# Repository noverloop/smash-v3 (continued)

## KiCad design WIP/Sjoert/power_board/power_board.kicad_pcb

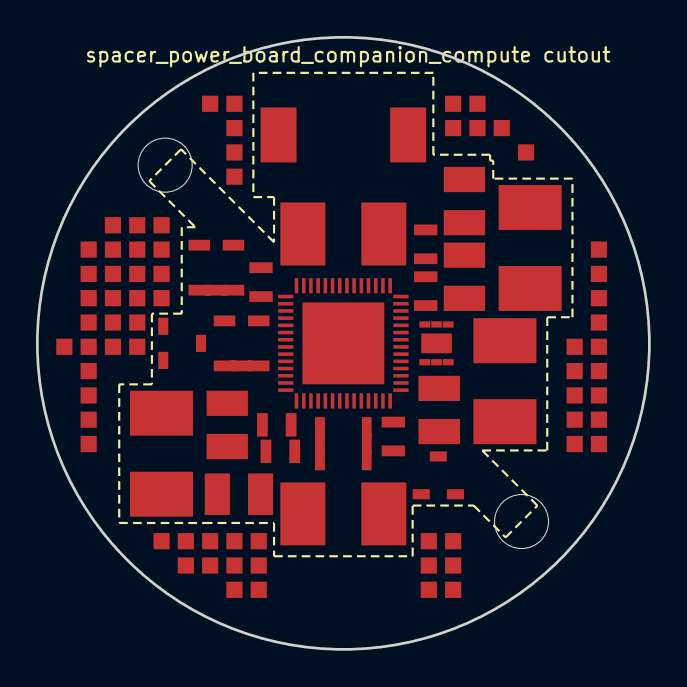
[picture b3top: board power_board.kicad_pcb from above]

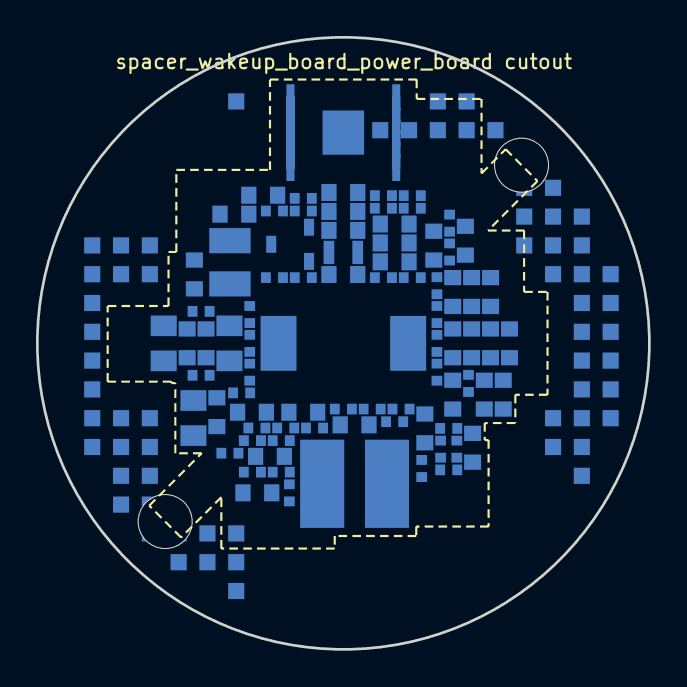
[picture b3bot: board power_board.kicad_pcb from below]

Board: 4 copper layers, 34.0 x 34.0 mm, 109 parts (84 on the bottom side), 95 nets, no tracks yet.

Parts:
CBAT1, CBAT2: T528W 100uF (7343-15 thinnest variant); Capacitor_Tantalum_SMD_CP_EIA-7343-15_Kemet-W
CBAT3: C-Series MIL-PRF-32535 X7R 0805 1uF; Capacitor_SMD_C_0805_2012Metric
C_BAT_BULK1, C_BAT_BULK2: T528W 470uF (7343-15 thinnest variant); Capacitor_Tantalum_SMD_CP_EIA-7343-15_Kemet-W
C_BOOST_COMP: C-Series MIL-PRF-32535 X7R 0603 220nF; Capacitor_SMD_C_0603_1608Metric
C_BOOST_OUT1: T528W 47uF (7343-15 thinnest variant); Capacitor_Tantalum_SMD_CP_EIA-7343-15_Kemet-W
C_BOOST_OUT2_1, C_BOOST_OUT2_2, C_BOOST_OUT2_3, C_BOOST_OUT2_4, C_BOOST_OUT2_5: C-Series MIL-PRF-32535 X7R 0603 2.2uF; Capacitor_SMD_C_0603_1608Metric
C_BOOST_OUT3: C0402 X7R 100nF; Capacitor_SMD_C_0402_1005Metric
C_BOOST_SS: C0402 X7R 47nF; Capacitor_SMD_C_0402_1005Metric
C_CAM_LDO_VAA_IN: C-Series MIL-PRF-32535 X7R 0805 1uF; Capacitor_SMD_C_0805_2012Metric
C_CAM_LDO_VAA_OUT_1, C_CAM_LDO_VAA_OUT_2: C-Series MIL-PRF-32535 X7R 0603 2.2uF; Capacitor_SMD_C_0603_1608Metric
C_CAM_LDO_VDD_IN: C-Series MIL-PRF-32535 X7R 0805 1uF; Capacitor_SMD_C_0805_2012Metric
C_CAM_LDO_VDD_OUT: C-Series MIL-PRF-32535 X7R 0603 2.2uF; Capacitor_SMD_C_0603_1608Metric
C_PMIC_0V9_1, C_PMIC_0V82_1, C_PMIC_1V8_1, C_PMIC_3V3_1: T491T 22uF (3528-12 thinnest variant); Capacitor_Tantalum_SMD_CP_EIA-3528-12_Kemet-T
C_PMIC_0V9_2, C_PMIC_0V82_2, C_PMIC_1V2_2, C_PMIC_1V8_2, C_PMIC_2V8_2, C_PMIC_3V3_2: C0402 X7R 100nF; Capacitor_SMD_C_0402_1005Metric
C_PMIC_1V2_1_1, C_PMIC_1V2_1_2, C_PMIC_1V2_1_3, C_PMIC_1V2_1_4, C_PMIC_1V2_1_5, C_PMIC_2V8_1_1, C_PMIC_2V8_1_2, C_PMIC_5V_FILT_1, C_PMIC_5V_FILT_2, C_PMIC_5V_FILT_3, C_PMIC_5V_FILT_4, C_PMIC_5V_FILT_5: C-Series MIL-PRF-32535 X7R 0603 2.2uF; Capacitor_SMD_C_0603_1608Metric
C_PMIC_INTLDO_1, C_PMIC_INTLDO_2: C-Series MIL-PRF-32535 X7R 0603 2.2uF; Capacitor_SMD_C_0603_1608Metric
C_PMIC_LDO1, C_PMIC_LDO2, C_PMIC_LDO4, C_PMIC_LDO6, C_PMIC_LDO7, C_PMIC_LDO8: C0402 X7R 100nF; Capacitor_SMD_C_0402_1005Metric
C_PMIC_VIN1: T491T 22uF (3528-12 thinnest variant); Capacitor_Tantalum_SMD_CP_EIA-3528-12_Kemet-T
C_PMIC_VIN2: C0402 X7R 100nF; Capacitor_SMD_C_0402_1005Metric
C_PMIC_VIN3, C_PMIC_VIN4, C_PMIC_VIN5, C_PMIC_VIN6: C-Series MIL-PRF-32535 X7R 0603 2.2uF; Capacitor_SMD_C_0603_1608Metric
C_PMIC_VLX7: C0402 X7R 100nF; Capacitor_SMD_C_0402_1005Metric
C_PMIC_VOUT7: C0402 X7R 100nF; Capacitor_SMD_C_0402_1005Metric
C_PMIC_VPP_1: T491T 22uF (3528-12 thinnest variant); Capacitor_Tantalum_SMD_CP_EIA-3528-12_Kemet-T
C_PMIC_VPP_2: C0402 X7R 100nF; Capacitor_SMD_C_0402_1005Metric
C_TMP1: C0402 X7R 100nF; Capacitor_SMD_C_0402_1005Metric
C_USB_VBUS_1, C_USB_VBUS_2, C_USB_VBUS_3, C_USB_VBUS_4, C_USB_VBUS_5: C-Series MIL-PRF-32535 X7R 0603 2.2uF; Capacitor_SMD_C_0603_1608Metric
D_BOOST_COMP: MBRS540T3G; DIOM7958X256N
D_USB_PWR: MBRS540T3G; DIOM7958X256N
J_power_board_spacer_power_board_companion_compute: LGA_lands; J_power_board_spacer_power_board_companion_compute
L_BOOST_COMP: 744043100; INDPM4848X280N
L_PMIC_BUCK1, L_PMIC_BUCK5, L_PMIC_BUCK6: TMS201210ALM-1R0MTAA; Inductor_SMD_L_2012_2.0x1.25mm
L_PMIC_BUCK2, L_PMIC_BUCK3, L_PMIC_BUCK4: TMS201210ALM-2R2MTAA; Inductor_SMD_L_2012_2.0x1.25mm
L_PMIC_FILT: TMS201210ALM-1R0MTAA; Inductor_SMD_L_2012_2.0x1.25mm
P_power_board_spacer_wakeup_board_power_board: LGA_lands; P_power_board_spacer_wakeup_board_power_board
Q_ISO: DMP6110SVT-7; SOT95P280X100-6N
Q_ISO_DRV: BSS138LT1G; SOT96P237X111-3N
Q_ISO_USB: BSS138LT1G; SOT96P237X111-3N
Q_USB_WAKE: BSS138LT1G; SOT96P237X111-3N
R_BAT1_ISO, R_BAT2_ISO, R_BAT3_ISO: CRCW0402 200m 1% e3; Resistor_SMD_R_0402_1005Metric
R_BOOST_COMP: CRCW0402 1.6k 1% e3; Resistor_SMD_R_0402_1005Metric
R_BOOST_FREQ: CRCW0402 176k 1% e3; Resistor_SMD_R_0402_1005Metric
R_BOOST_R1: CRCW0402 309k 1% e3; Resistor_SMD_R_0402_1005Metric
R_BOOST_R2: CRCW0402 100k 1% e3; Resistor_SMD_R_0402_1005Metric
R_ISO_EN_PD: CRCW0402 100k 1% e3; Resistor_SMD_R_0402_1005Metric
R_ISO_EN_S: CRCW0402 10k 1% e3; Resistor_SMD_R_0402_1005Metric
R_ISO_H: CRCW0402 100k 1% e3; Resistor_SMD_R_0402_1005Metric
R_ISO_L: CRCW0402 10k 1% e3; Resistor_SMD_R_0402_1005Metric
R_ISO_USB_H: CRCW0402 100k 1% e3; Resistor_SMD_R_0402_1005Metric
R_ISO_USB_L: CRCW0402 100k 1% e3; Resistor_SMD_R_0402_1005Metric
R_PMIC_NRST: CRCW0402 10k 1% e3; Resistor_SMD_R_0402_1005Metric
R_PMIC_PONKEY: CRCW0402 10k 1% e3; Resistor_SMD_R_0402_1005Metric
R_PMIC_PWRCTRL1_PD, R_PMIC_PWRCTRL2_PD, R_PMIC_PWRCTRL3_PD: CRCW0402 10k 1% e3; Resistor_SMD_R_0402_1005Metric
R_PMIC_PWR_OK: CRCW0402 10k 1% e3; Resistor_SMD_R_0402_1005Metric
R_PMIC_WAKEUP: CRCW0402 10k 1% e3; Resistor_SMD_R_0402_1005Metric
R_TMP1_ALERT_PU: CRCW0402 10k 1% e3; Resistor_SMD_R_0402_1005Metric
R_USBWK_G: CRCW0402 10k 1% e3; Resistor_SMD_R_0402_1005Metric
R_USBWK_PD: CRCW0402 100k 1% e3; Resistor_SMD_R_0402_1005Metric
U_CAM_LDO_VAA: LP5907MFX-2.8/NOPB; SOT95P280X145-5N
U_CAM_LDO_VDD: LP5907MFX-1.2/NOPB; SOT95P280X145-5N
U_COMP_BOOST: TPS61175PWPR; SOP65P640X120-15N
U_PMIC: STPMIC25APQR; QFN40P650X650X90-57N-D
U_TMP1: TMP117MAIDRVR; SON65P200X200X80-7N

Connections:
3V3: C_TMP1.1, J_power_board_spacer_power_board_compan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.1, J_power_board_spacer_power_board_compan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.57, J_power_board_spacer_power_board_compan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.68, P_power_board_spacer_wakeup_board_power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.1, P_power_board_spacer_wakeup_board_power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.55, P_power_board_spacer_wakeup_board_power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.62, R_PMIC_NRST.1, R_PMIC_PONKEY.1, R_PMIC_PWR_OK.1, R_PMIC_WAKEUP.1, U_PMIC.29, U_TMP1.5
ACTIVATE_CONFIRM: J_power_board_spacer_power_board_compan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.2, P_power_board_spacer_wakeup_board_power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.2
ACTIVATE_SET: J_power_board_spacer_power_board_compan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.3, P_power_board_spacer_wakeup_board_power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.3
BAT_CELL1_POS: P_power_board_spacer_wakeup_board_power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.4, R_BAT1_ISO.1
BAT_CELL2_POS: P_power_board_spacer_wakeup_board_power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.5, R_BAT2_ISO.1
BAT_CELL3_POS: P_power_board_spacer_wakeup_board_power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.6, R_BAT3_ISO.1
BAT_ISO_DRIVE: J_power_board_spacer_power_board_compan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.4, R_ISO_EN_S.1
BAT_ISO_EN: Q_ISO_DRV.1, Q_ISO_USB.3, R_ISO_EN_PD.1, R_ISO_EN_S.2
BAT_ISO_G: Q_ISO.3, R_ISO_H.2, R_ISO_L.1
BAT_ISO_GD: Q_ISO_DRV.3, R_ISO_L.2
BAT_ISO_USBG: Q_ISO_USB.1, R_ISO_USB_H.2, R_ISO_USB_L.1
BAT_PROT: CBAT1.1, CBAT2.1, CBAT3.1, D_USB_PWR.1, J_power_board_spacer_power_board_compan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.5, J_power_board_spacer_power_board_compan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.58, P_power_board_spacer_wakeup_board_power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.7, P_power_board_spacer_wakeup_board_power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.56, Q_ISO.4, R_ISO_H.1
BAT_RAW: C_BAT_BULK1.1, C_BAT_BULK2.1, P_power_board_spacer_wakeup_board_power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.8, P_power_board_spacer_wakeup_board_power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.57, Q_ISO.1, Q_ISO.2, Q_ISO.5, Q_ISO.6, R_BAT1_ISO.2, R_BAT2_ISO.2, R_BAT3_ISO.2
BOOT0: J_power_board_spacer_power_board_compan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.6, P_power_board_spacer_wakeup_board_power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.9
COMP_0V9: C_PMIC_0V9_1.1, C_PMIC_0V9_2.1, J_power_board_spacer_power_board_compan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.8, J_power_board_spacer_power_board_compan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.60, L_PMIC_BUCK1.2, U_PMIC.42
COMP_0V82: C_PMIC_0V82_1.1, C_PMIC_0V82_2.1, J_power_board_spacer_power_board_compan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.7, J_power_board_spacer_power_board_compan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.59, L_PMIC_BUCK5.2, U_PMIC.35
COMP_1V2: C_CAM_LDO_VDD_OUT.1, C_PMIC_1V2_1_1.1, C_PMIC_1V2_1_2.1, C_PMIC_1V2_1_3.1, C_PMIC_1V2_1_4.1, C_PMIC_1V2_1_5.1, C_PMIC_1V2_2.1, J_power_board_spacer_power_board_compan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.9, J_power_board_spacer_power_board_compan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.61, L_PMIC_BUCK6.2, U_CAM_LDO_VDD.5, U_PMIC.46
COMP_1V8: C_PMIC_1V8_1.1, C_PMIC_1V8_2.1, J_power_board_spacer_power_board_compan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.10, J_power_board_spacer_power_board_compan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.62, L_PMIC_BUCK4.2, P_power_board_spacer_wakeup_board_power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.10, P_power_board_spacer_wakeup_board_power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.58, U_PMIC.17
COMP_2V8: C_CAM_LDO_VAA_OUT_1.1, C_CAM_LDO_VAA_OUT_2.1, C_PMIC_2V8_1_1.1, C_PMIC_2V8_1_2.1, C_PMIC_2V8_2.1, J_power_board_spacer_power_board_compan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.11, J_power_board_spacer_power_board_compan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.63, U_CAM_LDO_VAA.5, U_PMIC.7
COMP_3V3: C_PMIC_3V3_1.1, C_PMIC_3V3_2.1, J_power_board_spacer_power_board_compan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.12, J_power_board_spacer_power_board_compan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.64, L_PMIC_BUCK2.2, R_TMP1_ALERT_PU.1, U_PMIC.28
COMP_5V: C_CAM_LDO_VAA_IN.1, C_CAM_LDO_VDD_IN.1, C_PMIC_5V_FILT_1.1, C_PMIC_5V_FILT_2.1, C_PMIC_5V_FILT_3.1, C_PMIC_5V_FILT_4.1, C_PMIC_5V_FILT_5.1, C_PMIC_VIN1.1, C_PMIC_VIN2.1, C_PMIC_VIN3.1, C_PMIC_VIN4.1, C_PMIC_VIN5.1, C_PMIC_VIN6.1, J_power_board_spacer_power_board_compan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.13, J_power_board_spacer_power_board_compan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.65, L_PMIC_FILT.2, P_power_board_spacer_wakeup_board_power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.11, P_power_board_spacer_wakeup_board_power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.59, U_CAM_LDO_VAA.1, U_CAM_LDO_VAA.3, U_CAM_LDO_VDD.1, U_CAM_LDO_VDD.3, U_PMIC.3, U_PMIC.6, U_PMIC.11, U_PMIC.15, U_PMIC.20, U_PMIC.24, U_PMIC.25, U_PMIC.38, U_PMIC.39, U_PMIC.43, U_PMIC.44, U_PMIC.49, U_PMIC.50
COMP_5V_COMP: R_BOOST_COMP.1, U_COMP_BOOST.8
COMP_5V_COMP_C: C_BOOST_COMP.1, R_BOOST_COMP.2
COMP_5V_FB: R_BOOST_R1.2, R_BOOST_R2.1, U_COMP_BOOST.9
COMP_5V_FREQ: R_BOOST_FREQ.1, U_COMP_BOOST.10
COMP_5V_RAW: C_BOOST_OUT1.1, C_BOOST_OUT2_1.1, C_BOOST_OUT2_2.1, C_BOOST_OUT2_3.1, C_BOOST_OUT2_4.1, C_BOOST_OUT2_5.1, C_BOOST_OUT3.1, D_BOOST_COMP.1, L_PMIC_FILT.1, P_power_board_spacer_wakeup_board_power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.12, P_power_board_spacer_wakeup_board_power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.60, R_BOOST_R1.1
COMP_5V_SS: C_BOOST_SS.1, U_COMP_BOOST.5
COMP_5V_SW: D_BOOST_COMP.2, L_BOOST_COMP.2, U_COMP_BOOST.1, U_COMP_BOOST.2
COMP_OUT: J_power_board_spacer_power_board_compan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.14, P_power_board_spacer_wakeup_board_power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.13
COMP_SWDCLK: J_power_board_spacer_power_board_compan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.15, P_power_board_spacer_wakeup_board_power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.14
COMP_SWDIO: J_power_board_spacer_power_board_compan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.16, P_power_board_spacer_wakeup_board_power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.15
COMP_VPP: C_PMIC_VPP_1.1, C_PMIC_VPP_2.1, J_power_board_spacer_power_board_compan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.17, J_power_board_spacer_power_board_compan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.66, L_PMIC_BUCK3.2, U_PMIC.21
EXT_CAN_RX: J_power_board_spacer_power_board_compan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.18, P_power_board_spacer_wakeup_board_power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.16
EXT_CAN_TX: J_power_board_spacer_power_board_compan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.19, P_power_board_spacer_wakeup_board_power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.17
FLEX_GND: CBAT1.2, CBAT2.2, CBAT3.2, C_BAT_BULK1.2, C_BAT_BULK2.2, C_BOOST_COMP.2, C_BOOST_OUT1.2, C_BOOST_OUT2_1.2, C_BOOST_OUT2_2.2, C_BOOST_OUT2_3.2, C_BOOST_OUT2_4.2, C_BOOST_OUT2_5.2, C_BOOST_OUT3.2, C_BOOST_SS.2, C_CAM_LDO_VAA_IN.2, C_CAM_LDO_VAA_OUT_1.2, C_CAM_LDO_VAA_OUT_2.2, C_CAM_LDO_VDD_IN.2, C_CAM_LDO_VDD_OUT.2, C_PMIC_0V9_1.2, C_PMIC_0V9_2.2, C_PMIC_0V82_1.2, C_PMIC_0V82_2.2, C_PMIC_1V2_1_1.2, C_PMIC_1V2_1_2.2, C_PMIC_1V2_1_3.2, C_PMIC_1V2_1_4.2, C_PMIC_1V2_1_5.2, C_PMIC_1V2_2.2, C_PMIC_1V8_1.2, C_PMIC_1V8_2.2, C_PMIC_2V8_1_1.2, C_PMIC_2V8_1_2.2, C_PMIC_2V8_2.2, C_PMIC_3V3_1.2, C_PMIC_3V3_2.2, C_PMIC_5V_FILT_1.2, C_PMIC_5V_FILT_2.2, C_PMIC_5V_FILT_3.2, C_PMIC_5V_FILT_4.2, C_PMIC_5V_FILT_5.2, C_PMIC_INTLDO_1.2, C_PMIC_INTLDO_2.2, C_PMIC_LDO1.2, C_PMIC_LDO2.2, C_PMIC_LDO4.2, C_PMIC_LDO6.2, C_PMIC_LDO7.2, C_PMIC_LDO8.2, C_PMIC_VIN1.2, C_PMIC_VIN2.2, C_PMIC_VIN3.2, C_PMIC_VIN4.2, C_PMIC_VIN5.2, C_PMIC_VIN6.2, C_PMIC_VLX7.2, C_PMIC_VOUT7.2, C_PMIC_VPP_1.2, C_PMIC_VPP_2.2, C_TMP1.2, C_USB_VBUS_1.2, C_USB_VBUS_2.2, C_USB_VBUS_3.2, C_USB_VBUS_4.2, C_USB_VBUS_5.2, J_power_board_spacer_power_board_compan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.20, P_power_board_spacer_wakeup_board_power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.18, P_power_board_spacer_wakeup_board_power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.63, Q_ISO_DRV.2, Q_ISO_USB.2, Q_USB_WAKE.2, R_BOOST_FREQ.2, R_BOOST_R2.2, R_ISO_EN_PD.2, R_ISO_USB_L.2, R_PMIC_PWRCTRL1_PD.2, R_PMIC_PWRCTRL2_PD.2, R_PMIC_PWRCTRL3_PD.2, R_USBWK_PD.2, U_CAM_LDO_VAA.2, U_CAM_LDO_VDD.2, U_COMP_BOOST.6, U_COMP_BOOST.7, U_COMP_BOOST.11, U_COMP_BOOST.12, U_COMP_BOOST.13, U_COMP_BOOST.14, U_COMP_BOOST.15, U_PMIC.9, U_PMIC.10, U_PMIC.18, U_PMIC.22, U_PMIC.27, U_PMIC.36, U_PMIC.41, U_PMIC.47, U_PMIC.52, U_PMIC.57, U_TMP1.2, U_TMP1.4, U_TMP1.7
GPIO_EXT_0: J_power_board_spacer_power_board_compan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.21, P_power_board_spacer_wakeup_board_power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.19
GPIO_EXT_1: J_power_board_spacer_power_board_compan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.22, P_power_board_spacer_wakeup_board_power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.20
GPIO_EXT_2: J_power_board_spacer_power_board_compan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.23, P_power_board_spacer_wakeup_board_power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.21
GPIO_EXT_3: J_power_board_spacer_power_board_compan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.24, P_power_board_spacer_wakeup_board_power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.22
H3LIS_INT1: J_power_board_spacer_power_board_compan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.25, P_power_board_spacer_wakeup_board_power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.23
I2C2_SCL: J_power_board_spacer_power_board_compan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.26, P_power_board_spacer_wakeup_board_power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.24, U_PMIC.33, U_TMP1.1
I2C2_SDA: J_power_board_spacer_power_board_compan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.27, P_power_board_spacer_wakeup_board_power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.25, U_PMIC.34, U_TMP1.6
I2C3_SCL: J_power_board_spacer_power_board_compan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.28, P_power_board_spacer_wakeup_board_power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.26
I2C3_SDA: J_power_board_spacer_power_board_compan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.29, P_power_board_spacer_wakeup_board_power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.27
IMU1_INT: J_power_board_spacer_power_board_compan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.30, P_power_board_spacer_wakeup_board_power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.28
IMU2_INT: J_power_board_spacer_power_board_compan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.31, P_power_board_spacer_wakeup_board_power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.29
IMU3_INT: J_power_board_spacer_power_board_compan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.32, P_power_board_spacer_wakeup_board_power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.30
IR_TX: J_power_board_spacer_power_board_compan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.33, P_power_board_spacer_wakeup_board_power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.31
IR_WAKE: J_power_board_spacer_power_board_compan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.34, P_power_board_spacer_wakeup_board_power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.32
MAG_DRDY: J_power_board_spacer_power_board_compan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.35, P_power_board_spacer_wakeup_board_power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.33
MAIN_SW_GATE: P_power_board_spacer_wakeup_board_power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.34, Q_USB_WAKE.3
NRST: J_power_board_spacer_power_board_compan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.36, P_power_board_spacer_wakeup_board_power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.35
PMIC_INTLDO: C_PMIC_INTLDO_1.1, C_PMIC_INTLDO_2.1, U_PMIC.8
PMIC_LDO1_TERM: C_PMIC_LDO1.1, U_PMIC.14
PMIC_LDO2_TERM: C_PMIC_LDO2.1, U_PMIC.16
PMIC_LDO4_TERM: C_PMIC_LDO4.1, U_PMIC.13
PMIC_LDO6_TERM: C_PMIC_LDO6.1, U_PMIC.5
PMIC_LDO7_TERM: C_PMIC_LDO7.1, U_PMIC.4
PMIC_LDO8_TERM: C_PMIC_LDO8.1, U_PMIC.2
PMIC_NRST: R_PMIC_NRST.2, U_PMIC.31
PMIC_PONKEY: R_PMIC_PONKEY.2, U_PMIC.1
PMIC_PWRCTRL1: R_PMIC_PWRCTRL1_PD.1, U_PMIC.56
PMIC_PWRCTRL2: R_PMIC_PWRCTRL2_PD.1, U_PMIC.55
PMIC_PWRCTRL3: R_PMIC_PWRCTRL3_PD.1, U_PMIC.54
PMIC_PWR_OK: J_power_board_spacer_power_board_compan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.37, R_PMIC_PWR_OK.2, U_PMIC.32
PMIC_SW1: L_PMIC_BUCK1.1, U_PMIC.40
PMIC_SW2: L_PMIC_BUCK2.1, U_PMIC.26
PMIC_SW3: L_PMIC_BUCK3.1, U_PMIC.23
PMIC_SW4: L_PMIC_BUCK4.1, U_PMIC.19
PMIC_SW5: L_PMIC_BUCK5.1, U_PMIC.37
PMIC_SW6: L_PMIC_BUCK6.1, U_PMIC.48
PMIC_VLX7_TERM: C_PMIC_VLX7.1, U_PMIC.51
PMIC_VOUT7_TERM: C_PMIC_VOUT7.1, U_PMIC.53
PMIC_WAKEUP: R_PMIC_WAKEUP.2, U_PMIC.30
PWR_HOLD: J_power_board_spacer_power_board_compan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.38, P_power_board_spacer_wakeup_board_power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.36
REG_IN_MAIN: L_BOOST_COMP.1, P_power_board_spacer_wakeup_board_power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.37, P_power_board_spacer_wakeup_board_power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.61, U_COMP_BOOST.3, U_COMP_BOOST.4
SWO: J_power_board_spacer_power_board_compan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.39, P_power_board_spacer_wakeup_board_power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.38
SYS_I2C_SCL: J_power_board_spacer_power_board_compan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.40, P_power_board_spacer_wakeup_board_power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.39
SYS_I2C_SDA: J_power_board_spacer_power_board_compan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.41, P_power_board_spacer_wakeup_board_power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.40
SYS_SPI_CS_FIN: J_power_board_spacer_power_board_compan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.42, P_power_board_spacer_wakeup_board_power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.41
SYS_SPI_MISO: J_power_board_spacer_power_board_compan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.43, P_power_board_spacer_wakeup_board_power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.42
SYS_SPI_MOSI: J_power_board_spacer_power_board_compan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.44, P_power_board_spacer_wakeup_board_power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.43
SYS_SPI_SCLK: J_power_board_spacer_power_board_compan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.45, P_power_board_spacer_wakeup_board_power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.44
TMP1_ALERT: J_power_board_spacer_power_board_compan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.46, R_TMP1_ALERT_PU.2, U_TMP1.3
USBWK_GATE: P_power_board_spacer_wakeup_board_power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.45, Q_USB_WAKE.1, R_USBWK_G.2, R_USBWK_PD.1
USB_VBUS: C_USB_VBUS_1.1, C_USB_VBUS_2.1, C_USB_VBUS_3.1, C_USB_VBUS_4.1, C_USB_VBUS_5.1, D_USB_PWR.2, J_power_board_spacer_power_board_compan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.47, J_power_board_spacer_power_board_compan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.67, R_ISO_USB_H.1, R_USBWK_G.1
WBA_BOOT0: J_power_board_spacer_power_board_compan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.48, P_power_board_spacer_wakeup_board_power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.46
WBA_HCI_IRQ: J_power_board_spacer_power_board_compan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.49, P_power_board_spacer_wakeup_board_power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.47
WBA_HCI_MISO: J_power_board_spacer_power_board_compan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.50, P_power_board_spacer_wakeup_board_power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.48
WBA_HCI_MOSI: J_power_board_spacer_power_board_compan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.51, P_power_board_spacer_wakeup_board_power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.49
WBA_HCI_NSS: J_power_board_spacer_power_board_compan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.52, P_power_board_spacer_wakeup_board_power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.50
WBA_HCI_SCK: J_power_board_spacer_power_board_compan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.53, P_power_board_spacer_wakeup_board_power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.51
WBA_RST_CMD: J_power_board_spacer_power_board_compan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.54, P_power_board_spacer_wakeup_board_power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.52
WBA_UART_RX: J_power_board_spacer_power_board_compan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.55, P_power_board_spacer_wakeup_board_power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.53
WBA_UART_TX: J_power_board_spacer_power_board_compan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.56, P_power_board_spacer_wakeup_board_power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.54
